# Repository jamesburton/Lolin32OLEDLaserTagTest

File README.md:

# Lolin32 OLED Laser Tag

Reverse-engineering, decoding, and transmitting **Vatos** infrared laser-tag
signals across two ESP32 boards:

- **Lolin32 OLED** (ESP32 + 128×32 SSD1306) — IR monitor / decoder / transmitter
  and the C# trainer feeder. Reads NEC remotes and Vatos shots to the OLED, and
  fires Vatos shots via an IR LED.
- **ESP32-S3-Matrix** (ESP32-S3 + 8×8 WS2812) — a wearable **target**: idles in
  a rainbow, tracks its own health, flashes the firing team's colour and goes
  briefly dark when hit, and holds dark when its health reaches zero.

Both boards support **wireless OTA updates and UDP telemetry** (see
[Wireless](#wireless)). A **network control plane** (REST + UDP) configures and
controls devices, with a **.NET client library** on the host side (see
[Control plane](#control-plane-v2)). Shared logic lives in libraries:
`lib/Vatos` (decode/encode), `lib/IrFramer` (IR edge framing), `lib/TagNet`
(WiFi + OTA + HTTP + UDP), and `lib/ControlProto` (the protocol-agnostic wire
codec for the control plane).

> The Vatos IR protocol is not documented publicly; the protocol description in
> `docs/gun-protocol.md` was reverse-engineered from scratch in this project.

---

## Table of contents

- [What it does](#what-it-does)
- [Hardware](#hardware)
- [Build, flash, monitor](#build-flash-monitor)
- [Wireless](#wireless)
- [Control plane (V2)](#control-plane-v2)
- [How it works](#how-it-works)
- [The Vatos protocol (reverse-engineered)](#the-vatos-protocol-reverse-engineered)
- [The Vatos library](#the-vatos-library)
- [The C# signal trainer](#the-c-signal-trainer)
- [The journey (how we got here)](#the-journey-how-we-got-here)
- [Repository layout](#repository-layout)
- [Future work](#future-work)

---

## What it does

- **Receives** 38 kHz IR and decodes it live:
  - **NEC** remotes → `address:command` (e.g. `0707:04`)
  - **Vatos** laser-tag shots → `team` + `damage` (e.g. `Blue 2`)
- **Displays** the decode on the on-board OLED, with a blink LED on every hit.
- **Transmits** valid Vatos shots via an IR LED (38 kHz carrier, correct frame
  + checksum), triggered by the BOOT button or any byte over serial.
- **Trains/recognises** signals from a PC via the C# `IrSignalTrainer` app,
  matching NEC codes exactly and other protocols by full-frame fingerprint.
- **Networks** the target: broadcasts discovery heartbeats and hit/state
  telemetry over UDP, serves a JSON REST API for config/control, accepts
  low-latency UDP control broadcasts, and is driven from a host-side **.NET
  client library** (see [Control plane](#control-plane-v2)).

---

## Hardware

### Carrier PCB (ESP32-S3-Matrix target)

A custom 100×80 mm 2-layer carrier board for the S3 target lives in
[`hardware/lasertag-carrier/`](hardware/lasertag-carrier/): socketed
ESP32-S3-Matrix, MAX98357A audio, microSD, IR RX + transistor IR-TX driver,
WS2812 strip output, OLED header, GP2 role selector, power switch and M3
mounting holes.

- **How to build/assemble it** (stage-by-stage, core vs optional blocks,
  jumper settings, bring-up):
  [`instructions/BUILD_LASERTAG_CARRIER_ESP32_MATRIX.md`](instructions/BUILD_LASERTAG_CARRIER_ESP32_MATRIX.md)
- **How it was made** (code → perf-board → Gerbers, tools/tips/gotchas):
  [`PCB_FROM_PLATFORMIO.md`](PCB_FROM_PLATFORMIO.md)
- **Fab package** (PCBWay-ready Gerber zip):
  [`hardware/lasertag-carrier/fab/lasertag-carrier-rev1-gerbers.zip`](hardware/lasertag-carrier/fab/lasertag-carrier-rev1-gerbers.zip),
  also attached to the
  [`pcb-carrier-rev1` release](../../releases/tag/pcb-carrier-rev1)
- **BOM**: [`hardware/lasertag-carrier/bom.csv`](hardware/lasertag-carrier/bom.csv);
  circuit spec: `.docs/pcb-blocks.md`
- **Ordering from PCBWay?** New users can use this referral link for **$5 off
  their first order**: <https://pcbway.com/g/2F9n3B>

### Lolin32 OLED (monitor / decoder / transmitter)

| Function | Pin | Notes |
| -------- | --- | ----- |
| OLED I²C | SDA = GPIO5, SCL = GPIO4 | SSD1306, **128×32**, address `0x3C` |
| IR receiver (VS1838B) | OUT = GPIO25 | demodulating; idles HIGH, pulses LOW |
| Activity LED | GPIO26 | blinks ~80 ms on each received frame |
| IR transmit LED | GPIO13 | 38 kHz carrier via the LEDC peripheral |
| Test-shot trigger | GPIO0 (BOOT) **or** serial | any serial line also fires a shot |

### ESP32-S3-Matrix (target)

| Function | Pin | Notes |
| -------- | --- | ----- |
| 8×8 WS2812 matrix | GPIO14 | on-board, 64 LEDs (NeoPixel) |
| IR receiver (VS1838B) | OUT = GPIO1 | GPIO10–14 are taken by the IMU/matrix |
| Activity LED | GPIO7 | blinks on each received frame |
| (reserved) | GPIO10–13 | on-board QMI8658 IMU |

Behaviour: rainbow when idle → on a Vatos hit, subtract the shot's damage from
its health (**max health 32**), flash the firing team's colour (Blue/Red/Green/White)
4×, then go dark for a brief configurable "stunned" interval (default ~1–5 s;
tune via the control plane) → resume rainbow, keeping accumulated damage. The
**4 central columns** of the 8×8 matrix form a **health bar**: they deplete
top-down as health drops (outer 4 columns stay rainbow). At **0 health** it
holds dark ("dead") until a respawn / reset. The device is **authoritative for
its own health** and emits `EVT hit` / `EVT state` telemetry as it changes (see
[Control plane](#control-plane-v2)). Matrix current is capped to 500 mA
(`setMaxPowerInVoltsAndMilliamps`) for USB safety.

Notes:

- The on-board OLED on this unit is a **128×32** SSD1306 (not the 128×64 the
  Lolin32 normally ships with). Driving it as 128×64 renders garbled,
  interlaced text — the `src/display_test.cpp` diagnostic cycles candidate
  driver/geometry configs to identify the right one.
- The OLED is **not** on the ESP32 default I²C pins, so `Wire.begin(5, 4)` is
  required.
- The receiver/transmit/indicator LEDs in this build are driven **without series
  resistors** at the ESP32's minimum drive strength (`GPIO_DRIVE_CAP_0`, ~5 mA)
  to protect the pins. This is fine for bench/loopback testing but limits IR
  transmit range — a transistor driver + resistor is needed for real range.

---

## Build, flash, monitor

[PlatformIO](https://platformio.org/) project (Arduino framework; boards
`lolin32` and `esp32-s3-devkitc-1`, plus a `native` env for unit tests).

```sh
pio run -e lolin32                                   # build
pio run -e lolin32 -t upload --upload-port COM14     # flash
pio device monitor -p COM14 -b 115200                # serial monitor
```

Environments:

- `lolin32` — Lolin32 firmware (`src/main.cpp`).
- `lolin32_displaytest` — the OLED config finder (`src/display_test.cpp`).
- `esp32-s3-matrix` — Matrix target firmware (`src/matrix_main.cpp`).
- `native` — host-compiled unit tests for `lib/ControlProto` (no board).
- `*-ota` — wireless-upload variants (see [Wireless](#wireless)).

```sh
pio run -e esp32-s3-matrix -t upload --upload-port COM7   # flash the Matrix
pio test -e native                                        # run ControlProto unit tests
```

### Flashing workaround (Lolin32)

This particular board has **no BOOT/EN buttons** and its USB auto-reset into the
bootloader is unreliable, so uploads may fail with
`Wrong boot mode detected (0x17)`. To flash:

1. Jumper **GPIO0 → GND**.
2. Run the upload — the chip now enters download mode and flashes.
3. **Remove the GPIO0–GND jumper** and reset (re-plug USB) so it boots normally.

If the board disappears from Windows entirely, unplug/replug the USB to
re-enumerate the CP210x serial port.

---

## Wireless

Both firmware targets bring up WiFi, ArduinoOTA, and UDP telemetry via the
shared `lib/TagNet` library.

### Set WiFi credentials (over serial)

Credentials are stored in NVS, set with serial commands (no rebuild):

```powershell
./tools/set-wifi.ps1 -Port COM14 -Ssid "MyNetwork" -Password "s3cret"
```

or manually in a serial monitor: `ssid <name>`, `pass <pw>`, `wifi-save`
(also `wifi-status`, `wifi-clear`). The board prints its IP once connected.

### Board-config overrides (cfg command)

A whitelisted subset of board-profile fields can be overridden at runtime
without a rebuild:

```
cfg <key> <value>
```

Examples: `cfg matrixOrder 1`, `cfg matrixPin 27`, `cfg activityLedPin 26`.
Changes are saved to NVS and applied on the next reboot.

### OTA updates

After one USB flash + WiFi provisioning, update over the air — no cable, no
GPIO0 jumper.

**For the S3 fleet, prefer the host's `ota` command** (see
[Game manager](#game-manager-host)): every board now runs 2.1.0, which serves
`POST /api/update`, so `ota all` flashes the whole fleet over HTTP with no
Python and no per-board IP chasing. The espota route below is now only needed
to **bootstrap a board running pre-2.1.0 firmware** (it has no `/api/update`),
and for the Lolin32.

```sh
pio run -e lolin32-ota -t upload          # -> lasertag-lolin32 (IP in platformio.ini)
pio run -e esp32-s3-matrix-ota -t upload  # -> lasertag-matrix  (IP in platformio.ini)
```

> ⚠ `ota all` sends **one binary to every online outdated board** and cannot
> tell an ESP32 from an ESP32-S3 (heartbeats carry no chip field). With the
> **Lolin32 (ESP32)** on the network alongside the S3 fleet, target it
> explicitly with `ota <id>` rather than `all`.

Both `*-ota` envs target the boards' **IP addresses** in `platformio.ini`.
mDNS (`lasertag-*.local`) resolves fine for ping/REST on this dev machine, but
espota is unreliable with mDNS names, so OTA sticks to IPs — resolve the
current one with `ping lasertag-matrix.local` (the matrix roams via DHCP) and
update `upload_port` if it changed, or set a DHCP reservation. OTA can take
several minutes over a weak link (low RSSI), but is reliable.

### Telemetry monitoring

Devices broadcast discovery heartbeats and hit/state telemetry as UDP lines on
port 4210 (see [Control plane](#control-plane-v2) for the grammar). The
`tools/TagMonitor` console app prints them raw:

```sh
dotnet run --project tools/TagMonitor
# lasertag-matrix HB id=752b38 ip=192.168.1.34 fw=2.1.0 team=2 mode=idle hp=32 online=1
# lasertag-matrix EVT hit victim=752b38 shooterTeam=2 dmg=2 proto=vatos hp=30 ts=12345
```

> `mode=` in a heartbeat is the board's **role** (`idle`/`target`/`scoreboard`),
> **not** the match phase — a board reads `mode=idle` throughout a running
> match. There is no per-board match-phase readback; the host is authoritative.

**Discovering boards:** listen to the heartbeat roster (TagMonitor, the host's
`devices`, or either manager) and give it **~30 s**. Don't port-scan the subnet
— it misses boards that answer slowly, and every board roams on DHCP, so any IP
written down here or in `platformio.ini` may already belong to something else.

> **No telemetry but REST works?** That's a missing inbound firewall rule **or**
> a lossy weak-RSSI link. Rule out the firewall with `tools/setup-firewall.ps1`
> (Windows, self-elevating) / `tools/setup-firewall.sh` (Linux/macOS).

---

## Control plane (V2)

A protocol- and mode-agnostic network layer for configuring, controlling, and
monitoring devices. **REST** (reliable, JSON) handles config/CRUD/status; **UDP**
(fast, fire-and-forget on port 4210) handles discovery, telemetry, and
low-latency broadcast control. Devices decode IR into a generic `TagEvent`
(behind an `IrProtocol` abstraction — Vatos is the first protocol) and teams are
a generic indexed set, so game modes and the host never hard-code Vatos.

The full design and the authoritative wire contract (with golden test vectors)
live in
[`docs/superpowers/specs/`](docs/superpowers/specs/2026-06-15-control-plane-contract.md).

### REST API (served by the device)

| Method | Route | Purpose |
| ------ | ----- | ------- |
| `GET` | `/api/status` | live runtime status (mode, hp, team, online, fw, uptime, rssi) |
| `GET` | `/api/config` | persisted config (deviceId, ownTeam, enabledTeams, protocolId, brightness, teamColours) |
| `PATCH` | `/api/config` | partial update; persists to NVS; unknown field → `400` |
| `POST` | `/api/mode` | set runtime `activeMode` + timings (not persisted) |
| `POST` | `/api/command` | one-shot actions: `identify`, `bright`, test `hit`, `debug` |

Identity + preferences persist in NVS; game state (mode, timings, health) is
runtime only, so a reboot returns the device to a neutral idle. **Write
requests must send `Content-Type: application/json`** — the ESP32 `WebServer`
discards a urlencoded body (curl's default); the .NET client sets the header
automatically. (`GET /` and `GET /cmd?c=` remain as deprecated aliases.)

### UDP line-protocol (port 4210)

One message per packet; device→broadcast lines are prefixed with the hostname.

```
HB  id=752b38 ip=192.168.1.24 fw=2.0.0 team=2 mode=idle hp=100 online=1   # heartbeat (~2 s)
EVT hit victim=752b38 shooterTeam=2 dmg=2 proto=vatos hp=80 ts=12345      # telemetry
EVT state s=stunned hp=80 ts=12500                                        # ready|idle|stunned|dead|respawn
CTL start ts=30000   |   CTL stop   |   CTL reset hp=100                  # host -> device control
```

`EVT`/`HB` come **from** the device; `CTL` is sent **to** devices. The device is
authoritative for its own health; the host tallies match state from the event
stream. Send `CTL` to the **subnet broadcast** (e.g. `192.168.1.255`) — the
limited broadcast `255.255.255.255` is not delivered on this LAN.

### .NET host library

`dotnet/LaserTag.Client` (net10.0) is the typed host client:

- `LaserTagClient` — REST client for `/api/*` (`GetStatusAsync`,
  `PatchConfigAsync`, `SetModeAsync`, `SendCommandAsync`, …).
- `UdpMessageParser` — parses `HB`/`EVT` lines into typed records; formats `CTL`.
- `DeviceRoster` — live roster with liveness timeout (6 s) + rejoin detection.
- `NetworkDiagnostics` — advisory firewall/port hints.

`dotnet/openapi/lasertag.yaml` describes the REST surface (for generating other
clients). `dotnet/LaserTag.Smoke` is a throwaway harness that exercises the
library against a live device; run it for a quick end-to-end check:

```sh
dotnet test  dotnet/LaserTag.sln                              # unit tests
dotnet run --project dotnet/LaserTag.Smoke -- 192.168.1.24 20 # live REST + UDP roster
```

### Game manager (host)

`dotnet/LaserTag.Host` orchestrates matches over the control plane (spec:
`docs/superpowers/specs/2026-07-12-game-manager-design.md`):

```sh
dotnet run --project dotnet/LaserTag.Host            # auto-detects the subnet broadcast
# devices | start dm 5m [--kill 5 --hit 1 --waves 30s] | start elim [--timer 10m]
# start chase <dur|--first N> [--min d] [--max d] [--gap d] [--penalty N] [--dark]
# score | stop | reset [id] | activate [id] | deactivate [id] | quit
# team <id|all> <0-4|none>  — assign a board's team (0/none = neutral target)
# teams split <n>           — deal the online roster round-robin into n sides
# fs ls|put|get|rm|play|startup <id> …  — manage sound clips in on-board flash
# fw [bin]                — fleet firmware table: running vs available (from the
#                           LTFW: marker embedded in firmware.bin)
# ota <id|all> [--force]  — push firmware over HTTP to online boards; `all`
#                           targets outdated boards only (--force re-pushes)
```

**Fleet OTA (firmware ≥ 2.1.0):** every board serves `POST /api/update`
(multipart firmware upload → verified flash → reboot) and a browser upload
form at `GET /update`, so updates work from the host CLI, a browser, or the
future phone app — no espota/python needed. Spec:
`docs/superpowers/specs/2026-07-27-fleet-ota-design.md`. Boards on older
firmware need one last espota flash to gain the endpoint.

### Sound clips in on-board flash (firmware ≥ 2.4.0)

Clips live in the board's **on-board flash**, in the partition table's
otherwise-unused 1.375 MB data partition (LittleFS). No microSD, no socket, no
wiring. Manage them remotely:

```sh
fs ls <id> [dir]              # storage usage + directory listing
fs put <id> <local> <remote>  # upload, e.g. fs put e45614 assets/sfx/startup-rise.wav /sfx/startup.wav
fs get <id> <remote> <local>  # download
fs rm  <id> <remote>          # delete (files only; directories are refused)
fs play <id> <remote>         # play a clip now
fs startup <id> <remote|none> # set/clear the power-on cue
```

REST equivalents on each board: `GET /api/files?path=`,
`POST|GET|DELETE /api/files/file?path=`, and
`POST /api/command {"cmd":"play","path":"…"}`.

**Clips must be 16 kHz / 16-bit / mono WAV** — the parser rejects anything else
rather than converting. Generate one with
`python tools/gen_sfx.py --wav out.wav --clip startup|death`, or convert any
source with
`ffmpeg -i in.mp3 -ac 1 -ar 16000 -sample_fmt s16 out.wav`.

**There is no clip length limit.** Playback streams from flash in chunks and
feeds the task watchdog, so clip size is bounded by the partition (~1.4 MB,
about four 10-second clips) rather than by free RAM. Both former limits are
gone: clips used to be capped at ~3 s by the watchdog, and at ~270 KB by having
to fit in the heap.

> **Startup sound defaults to none.** Set it per board with `fs startup`; it is
> stored as `startupSfx` and played once at the end of boot. An unset, missing
> or malformed clip is skipped silently so a board always comes up.

> Clips **survive firmware updates** — OTA replaces the app partition only.

> A clip that no config field references is reachable *only* via the API, which
> is how to keep a "secret" sound with no on-board trigger.

> Every caller-supplied path is validated on the device: absolute, no `..`
> segment. That check is the only thing between a LAN request and the
> filesystem, so it is unit-tested natively.

**microSD is optional and currently unproven.** The code remains (`sdprobe`,
`sdpins`, `sdscan` are useful hardware diagnostics), but no board here has ever
mounted a card — see the handoff for the electrical findings.

### Teams (firmware ≥ 2.2.0)### Teams (firmware ≥ 2.2.0)

A device's team lives in its **persisted config** (`ownTeam`), not the control
plane: a match reads each board's team from its heartbeat and snapshots it when
the lobby forms. Assign teams from any surface:

```sh
# Host CLI
team <id|all> <0-4|none>   # one board, or the whole roster
teams split <n>            # deal the online roster round-robin into n sides

# Web / Android manager: the team buttons on each Devices card
# JSON API
curl -X POST http://<host>:5080/api/team -H 'content-type: application/json' \
     -d '{"id":"752b38","team":1}'
```

**Team 0 = `none` = a neutral target, and it is the default.** A neutral board
is shootable by everyone, hits on it score for the *shooter's* team, and it can
never win a match — the right default for a target that isn't playing for a
side. This matches what the firmware has always done physically: it has never
own-team filtered, so every decoded shot damages the board that receives it.
Boards provisioned before 2.2.0 keep whatever team they were given (most were
2); `team all none` resets them.

> `teams split` uses a stable order (by device id), so the same fleet always
> splits the same way rather than reshuffling sides between matches.

> ⚠ **Teams take effect from the next match.** The lobby fixes each
> participant's team at start, so reassigning mid-round does not move a player —
> that would silently rewrite who the existing scores belonged to.

> ⚠ **The lobby is fixed at match start.** Devices that come online after the
> countdown are ignored for the rest of the match (a device that *drops and
> returns* does rejoin, and gets a re-issued `CTL start id=`).

Match rules live in `dotnet/LaserTag.Game` (`IGameMode`: Deathmatch,
Elimination, Chase — see `docs/superpowers/specs/2026-07-27-chase-mode-design.md`).
Scoring is per-team — the IR protocol carries the shooter's team, not a
player id. CTL grammar v2 (`countdown`, `gameover`, `activate`/`deactivate`,
optional `id=` addressing) is emitted by the host today.

Boards double as scoreboards during any match — the host pushes CTL Score
updates on change plus a 1 s live refresh, so a board's own OLED/matrix shows
the running score without extra wiring. A board can also run standalone as a
dedicated scoreboard outside of a match via `POST /api/mode {"mode":
"scoreboard"}`.

**Firmware compatibility:** firmware at or above this build enforces `id=`
addressing, so an `id=`-addressed `reset`/`start`/`activate`/`deactivate`
only reaches the targeted device. Boards still running older firmware ignore
the `id=` filter and apply addressed CTLs to every device on the arena —
reflash all boards to the current firmware before running a multi-device
match.

---

## Managers: web and Android

Two graphical front ends for running a game, alongside the console REPL. Both
render **the same screens from the same code** and run **the same match engine** —
they differ only in which machine the engine runs on.

```
        LaserTag.Ui (Blazor screens + IGameSession)
                    /                \
      LaserTag.Web                    LaserTag.App
   engine on the PC                engine on the phone
                    \                /
              LaserTag.Runtime (GameService, UDP listener, 4 Hz tick)
                    LaserTag.Game + LaserTag.Client
```

Screens: **Devices** (roster with identify/reset/activate per board), **Match**
(mode picker with per-mode parameters, start/stop), **Live** (scoreboard, player
table, event feed), **Firmware** (running-vs-available versions and one-tap OTA,
reusing the fleet-OTA pipeline).

### Web manager

```sh
dotnet run --project dotnet/LaserTag.Web            # http://<pc-ip>:5080
dotnet run --project dotnet/LaserTag.Web -- --broadcast 192.168.1.255
```

Binds `0.0.0.0:5080` over plain HTTP so any phone or laptop on the LAN can open
it — no install, and iPhone guests work too. A PC must be running at play time.

A JSON API sits alongside the UI for scripting:

| Endpoint | Purpose |
| -------- | ------- |
| `GET /api/devices` | Roster with team, hp, firmware, online |
| `GET /api/match` | Phase, clock, scores, players |
| `POST /api/match/start` | Body e.g. `{"mode":"chase","duration":"2m","firstTo":5}` |
| `POST /api/match/stop` | Stop the running match |
| `POST /api/control` | e.g. `{"kind":"activate","id":"eb20f8","t":1500}` |

### Android manager (the phone is the host)

```sh
dotnet build dotnet/LaserTag.App -f net10.0-android
dotnet publish dotnet/LaserTag.App -f net10.0-android -c Release -p:AndroidPackageFormat=apk
# -> dotnet/LaserTag.App/bin/Release/net10.0-android/publish/com.jamesburton.lasertag-Signed.apk
```

The phone binds UDP 4210, runs the engine and broadcasts CTL itself, so **no PC
is needed at play time** — the point of the exercise. Requires the
`maui-android` workload (`dotnet workload install maui-android`).

Two Android-specific traps are handled in code, both of which produce a
silently-empty roster rather than an error:

- **Multicast lock.** Android drops inbound broadcast UDP unless the app holds a
  `WifiManager.MulticastLock`. `AndroidMulticastGuard` holds one for the
  listener's lifetime; the manifest needs `CHANGE_WIFI_MULTICAST_STATE`.
- **MAUI never starts hosted services.** Unlike the Generic Host, `MauiApp`
  builds a service provider but does not run `IHostedService`, so the listener
  and tick loop are started explicitly in `App.OnStart`.

| Android app | Web manager |
| ----------- | ----------- |
|  |  |

> **Status:** the Android app **runs** — installed and driven on an Android 15
> emulator, where the shared screens render, navigation works and broadcast
> discovery picked up the right subnet. What is **still unverified** is the one
> thing that matters most: **receiving real telemetry**. An emulator sits behind
> NAT, so host broadcasts never reach it, and the multicast lock therefore could
> not be exercised. Treat the first run on a real phone, on the same Wi-Fi as
> the boards, as the true test.

## Board capability HAL

Each board is described by a compile-time `BoardProfile` struct (selected with
`-D BOARD_LOLIN32` or `-D BOARD_S3_MATRIX` in `platformio.ini`) that declares
its capabilities: IR rx/tx pins, hit-display type (WS2812 matrix, 3-pin RGB, or
none), OLED geometry, audio output (piezo or I2S DAC stub), and NVS storage.
Firmware and game-mode code target the HAL — `HitDisplay`, `IrTx`, `Sound` —
rather than raw pins, so the same game logic runs on any profiled board.

A whitelisted subset of profile fields (e.g. matrix data pin, pixel order,
activity LED pin) can be overridden at runtime via the `cfg <key> <value>`
serial command (see [Board-config overrides](#board-config-overrides-cfg-command));
overrides are persisted in NVS and applied at boot.

---

## How it works

### Receive path

An interrupt on the receiver pin timestamps every edge. Edges are grouped into
**frames** separated by ≥ 50 ms of silence (chosen so the gun's full-auto bursts
stay within one frame). Each completed frame is:

1. attempted as **NEC** (leader + 32 bits, validated by the command/inverse
   byte) → emits `NEC addr=0x.... cmd=0x..`;
2. otherwise, if it is 41 edges, attempted as **Vatos** → emits
   `VATOS team=N(name) dmg=N`;
3. always emitted raw as `FRAME n=.. data=L..,H..,...` for fingerprinting.

The optional decoded line is printed **before** the `FRAME` line so a consumer
can attach it to the frame that terminates the event.

> **Verified board-to-board (2026-07-29):** an IR-TX-equipped board firing at
> another decodes exactly — all four damage values cost exactly their damage,
> and all four shooter teams arrive correctly in `EVT hit shooterTeam=`.
> Two things to know when testing: range is very short on a raw GPIO drive
> (aim the boards at each other, close), and **shots arriving during the
> post-hit flash/stun window are ignored by design** (`applyHit` runs only in
> the rainbow idle state), so space test shots ~4 s apart — a rapid burst
> looks like a fault but isn't.

### Transmit path

`Vatos::encode()` builds the 41-symbol bit pattern for a `{team, damage}` shot
(including the correct checksum). The firmware then gates a 38 kHz LEDC carrier:
even symbols are IR bursts (carrier on), odd symbols are gaps, each lasting
~380 µs (`0`) or ~800 µs (`1`). Pointing the IR LED at the VS1838B closes a full
**loopback**: transmitted shots are received and decoded by the same board.

### Serial protocol (115 200 baud)

```
NEC addr=0x0707 cmd=0x04            # optional, precedes its FRAME
VATOS team=1(Blue) dmg=2           # optional, precedes its FRAME
FRAME n=75 data=L4520,H4490,...    # always; H/L = level held, value = µs
TX team=1(Blue) dmg=2              # printed when a shot is transmitted
```

---

## The Vatos protocol (reverse-engineered)

A Vatos shot is a **41-edge frame** on a ~38 kHz carrier: 21 IR bursts
interleaved with 20 gaps (it starts and ends with a burst). Every symbol is
short (~380 µs = `0`) or long (~800 µs = `1`); quantising at 600 µs gives a
stable 41-bit pattern.

The frame encodes the firing **team** and the shot's **damage** — *not* the
weapon:

| Field | Bits (MSB-first) | Values |
| ----- | ---------------- | ------ |
| Preamble / framing | 0–21 | constant |
| **Team** | 22–24 | Blue=`001`(1), Red=`010`(2), Green=`011`(3), White=`100`(4) |
| Separator | 25–29 | constant |
| **Damage** | 30–32 | `001`–`100` = damage 1–4 |
| Separator | 33–36 | constant `0000` |
| Checksum | 37–40 | fixed (nonlinear) function of team + damage |

### Key findings

- **It encodes damage, not weapon.** Per the manual: Pistol = 1, Shotgun = 2,
  SMG = 2, MG = 3, Rocket = 4. Because **Shotgun and SMG both deal damage 2,
  they transmit an identical frame** — no receiver can tell them apart. So each
  gun emits at most 4 distinct codes per team (4 teams × 4 damage = 16 total).
- **The audio is mislabelled on this unit:** the spoken "Machine Gun" / "Sub
  Machine Gun" names are swapped relative to the damage actually sent. Identify
  shots by damage, not the voice line.
- **Carrier is ~38 kHz**, confirmed because the (38 kHz) VS1838B demodulates the
  gun cleanly. No 56 kHz receiver needed.
- **Both bursts and gaps carry payload.** An early fingerprint that used only the
  gap durations collided distinct shots (for some teams, damage 2 and damage 3
  share gap patterns and differ only in the bursts). The working approach
  fingerprints/decodes the full frame.

The full derivation, the 16-code matrix, and the bit map are in
[`docs/gun-protocol.md`](docs/gun-protocol.md).

---

## The Vatos library

`lib/Vatos/` is a platform-independent decoder/encoder (no Arduino
dependencies — carrier generation lives in the caller):

```cpp
namespace Vatos {
  struct Shot { uint8_t team; uint8_t damage; };          // team 1-4, damage 1-4

  bool decode(const uint32_t *edgeDurationsUs, size_t count, Shot &out);
  bool encode(const Shot &shot, bool bits[FrameEdges]);    // FrameEdges == 41
  const char *teamName(uint8_t team);                      // "Blue".."White"
}
```

- `decode()` quantises 41 edge durations, validates the constant framing **and**
  the checksum, and extracts team + damage.
- `encode()` produces the 41-symbol pattern (even indices = bursts) for
  transmission, with the correct checksum from a 4×4 lookup table.

Both directions were verified by full **TX → IR → RX → decode** loopback across
multiple team/damage codes, and `decode()` was verified against real gun fire.

---

## RF (2.4 GHz) probe — CLOSED, no signal found

A side investigation into whether the Vatos kit also uses a 2.4 GHz link
alongside its IR. **Result: nothing was detected**, and the leading explanation
is that these gun-only units have no radio — see
[docs/rf-protocol.md](docs/rf-protocol.md) for the evidence and the retractions.

The tooling works and is kept for if the question reopens. An nRF24L01+ wired to
an ESP8266 (`pio run -e esp8266-rfprobe`) provides five serial commands:

| Command | Purpose |
| ------- | ------- |
| `selftest` | Reads back written registers — proves the SPI wiring |
| `scan [sweeps]` | Fast sweep of all 126 channels via the power detector |
| `watch from= to= ms=` | Dwells per channel; far more sensitive to short bursts |
| `dwell ch= secs=` | Camps on one channel, 100 ms buckets for event correlation |
| `sniff ch= rate= secs=` | Promiscuous capture (2-byte address, CRC off) |

Wiring: CE=GPIO4, CSN=GPIO5, SCK=GPIO14, MOSI=GPIO13, MISO=GPIO12, 3V3 with a
10 µF cap at the module. Captured `RF …` lines are analysed by the
**`LaserTag.Rf`** library (CRC16 validation, bit realignment, address recovery);
only a CRC-valid packet counts as a detection. Occupancy figures never do — that
lesson cost an evening and is written up in the findings doc.

## The C# signal trainer

`tools/IrSignalTrainer/` is a .NET console app that reads the board's serial
output and tags signals against named devices and buttons (see
[`tools/README.md`](tools/README.md)).

```sh
dotnet run --project tools/IrSignalTrainer            # COM14, signatures.json
```

- **NEC** signals match **exactly** on the decoded `address:command` code.
- **Other** signals (e.g. the gun, before firmware decoding existed) match on a
  quantised **full-frame** bit signature.
- `t` trains (device + button, 4 samples), `l` lists, `q` quits. The library is
  persisted to `signatures.json`.

`signatures.json` in the repo contains an example library trained on a TV remote
(NEC) and the Vatos gun.

---

## The journey (how we got here)

A condensed log of the build, because most of the value was in the process:

1. **Board bring-up.** Adapted the manufacturer OLED example to PlatformIO and
   verified the display + serial. Discovered the panel is 128×**32**, not
   128×64 — the cause of unreadable, interlaced text — using a config-finder
   sketch.
2. **Sensor selection.** Started with a KEYES photodiode + LM393 comparator
   board. It is not a demodulating receiver, so its output fragmented/merged and
   needed constant potentiometer tuning. Swapped to a **VS1838B**, which
   produced clean, decode-grade frames with no tuning. (See
   `docs/sensor-comparison.md`.)
3. **NEC decoding.** Added an NEC decoder to the firmware (OLED shows
   `addr:cmd`) and validated it against a TV remote (address `0x0707`).
4. **Cracking the gun.** The gun was not NEC. Captured frames, decoded the
   structure, and — crucially, with the owner's manual + the spotted audio/icon
   mismatch — realised the IR encodes **team + damage**, which explained an
   apparent "Shotgun = Machine Gun" collision (it is really Shotgun = SMG, both
   damage 2). Captured the full 4-team × 4-damage matrix and isolated the team,
   damage, and checksum bit-fields.
5. **Library + transmit.** Factored the decode/encode into `lib/Vatos/`, added a
   38 kHz IR transmitter, and verified the whole chain by loopback.

---

## Repository layout

```
platformio.ini            PlatformIO config (lolin32 / displaytest / matrix + OTA + native)
src/
  main.cpp                Lolin32: RX + NEC/Vatos decode, OLED, IR transmit
  matrix_main.cpp         ESP32-S3-Matrix: 8x8 LED target + V2 control plane
  display_test.cpp        OLED driver/geometry config finder (separate env)
lib/
  Vatos/                  Platform-independent Vatos decode/encode
  IrFramer/               Shared IR edge-framing (ISR + frame assembly)
  TagNet/                 Shared WiFi (serial creds) + OTA + UDP + HTTP server
  ControlProto/           Protocol-agnostic control-plane wire codec + TagEvent
  Board/                  Compile-time BoardProfile per board (pins, capabilities)
  HitDisplay/             WS2812 matrix / RGB hit-feedback output HAL
  IrTx/                   IR transmit HAL
  Sound/                  Sound cues (piezo; I2S DAC stub)
  BoardNvs/               NVS override load + cfg serial command
test/
  test_board/             Native unit tests for Board/BoardNvs
  test_controlproto/      Native (host-compiled) unit tests for ControlProto
dotnet/                   .NET 10 host ecosystem (LaserTag.sln)
  LaserTag.Client/        Typed REST + UDP client library (parser, roster, client)
  LaserTag.Client.Tests/  xUnit tests
  LaserTag.Smoke/         Throwaway live smoke harness
  openapi/lasertag.yaml   OpenAPI description of the REST surface
tools/
  IrSignalTrainer/        C# serial trainer + signature library
  TagMonitor/             C# UDP telemetry listener
  set-wifi.ps1            Provision WiFi credentials over serial
  setup-firewall.ps1/.sh  Check/fix the host firewall for UDP 4210 telemetry
docs/
  device-info.md          Lolin32 board pinout and OLED details
  sensor-comparison.md    KEYES comparator board vs VS1838B
  gun-protocol.md         The reverse-engineered Vatos IR protocol
  superpowers/specs/      Control-plane design + authoritative wire contract
signatures.json           Example trained signature library (TV remote + gun)
```

---

The V2 **control plane** (REST + UDP config/control/telemetry, device-side
health, the .NET client library) is in place. Next:

- **Firmware game-mode framework + "Team Colours" mode** — pluggable modes on
  top of the `activeMode`/timings plumbing already wired through the control
  plane.
- **Host scoring & orchestration** — tally match state from the `EVT` stream;
  multi-device game start/stop via `CTL` broadcasts.
- **.NET CLI + Claude skill** — a runnable CLI over `LaserTag.Client` (the
  library exists; its `CTL` sender must target the subnet broadcast), wrapped as
  a Claude skill.
- **Real transmit range** — a transistor driver + series resistor on the IR LED
  for gameplay distances rather than bench loopback.
- **Pin down the checksum formula** — currently a verified 4×4 lookup; the exact
  algorithm (symmetric in team+damage) is not yet derived.

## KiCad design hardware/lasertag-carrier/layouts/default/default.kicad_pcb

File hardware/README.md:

# hardware/ — KiCad PCB project

Custom carrier/breakout PCB for the laser-tag platform. Starts with the
**ESP32-S3-Matrix carrier** (full scope: audio, microSD, IR RX/TX, I2C OLED,
external WS2812 out, power in; optional separate level-shifter board).

## Source of truth
- **`../.docs/pcb-blocks.md`** — netlist-level block spec (pin-to-pin tables, BOM).
  KiCad generation is mechanical from these tables.
- **`../.docs/pcb-design.md`** — higher-level decisions + toolchain rationale.
- **`../.docs/handoff.md`** §Board BOM — the discrete circuitry summary.

The circuit was agreed 2026-07-04 (see the "RECONCILED" note in `pcb-blocks.md`):
IR TX on **GP37** (2N2222A + 33Ω from 5V driver), 0.1″ connectors throughout,
power LED, optional microSD LDO, audio SD hard-mute on a GP2 solder-jumper.

## Toolchain (see `pcb-design.md` for the full rationale)
- **Schematic = file-based** via `kicad-skip` (edits `.kicad_sch` S-expr) or SKiDL
  (code → netlist). **KiCad v10 has no schematic API**, so the MCP can't do this.
- **Exports** (Gerbers / BOM / DRC / netlist) via `kicad-cli` (KiCad 10.0.3 at
  `C:\Program Files\KiCad\10.0\bin\kicad-cli.exe`).
- **`kicad-mcp` is PCB-layout only** — registered in `../.mcp.json` for the later
  routing phase; needs a session reload to activate. Not used for schematic.
- **Wokwi `diagram.json`** (in `../sim/wokwi/`) is generated one-way from the KiCad
  netlist for firmware/wiring simulation.

`KICAD_SEARCH_PATHS` (in `../.mcp.json`) points here.

## Status
Scaffold. Schematic capture pending (next step: `kicad-skip`/SKiDL from the
`pcb-blocks.md` tables). Layout/routing/fab gated on the pin freeze (handoff #1/#5,
now largely landed).

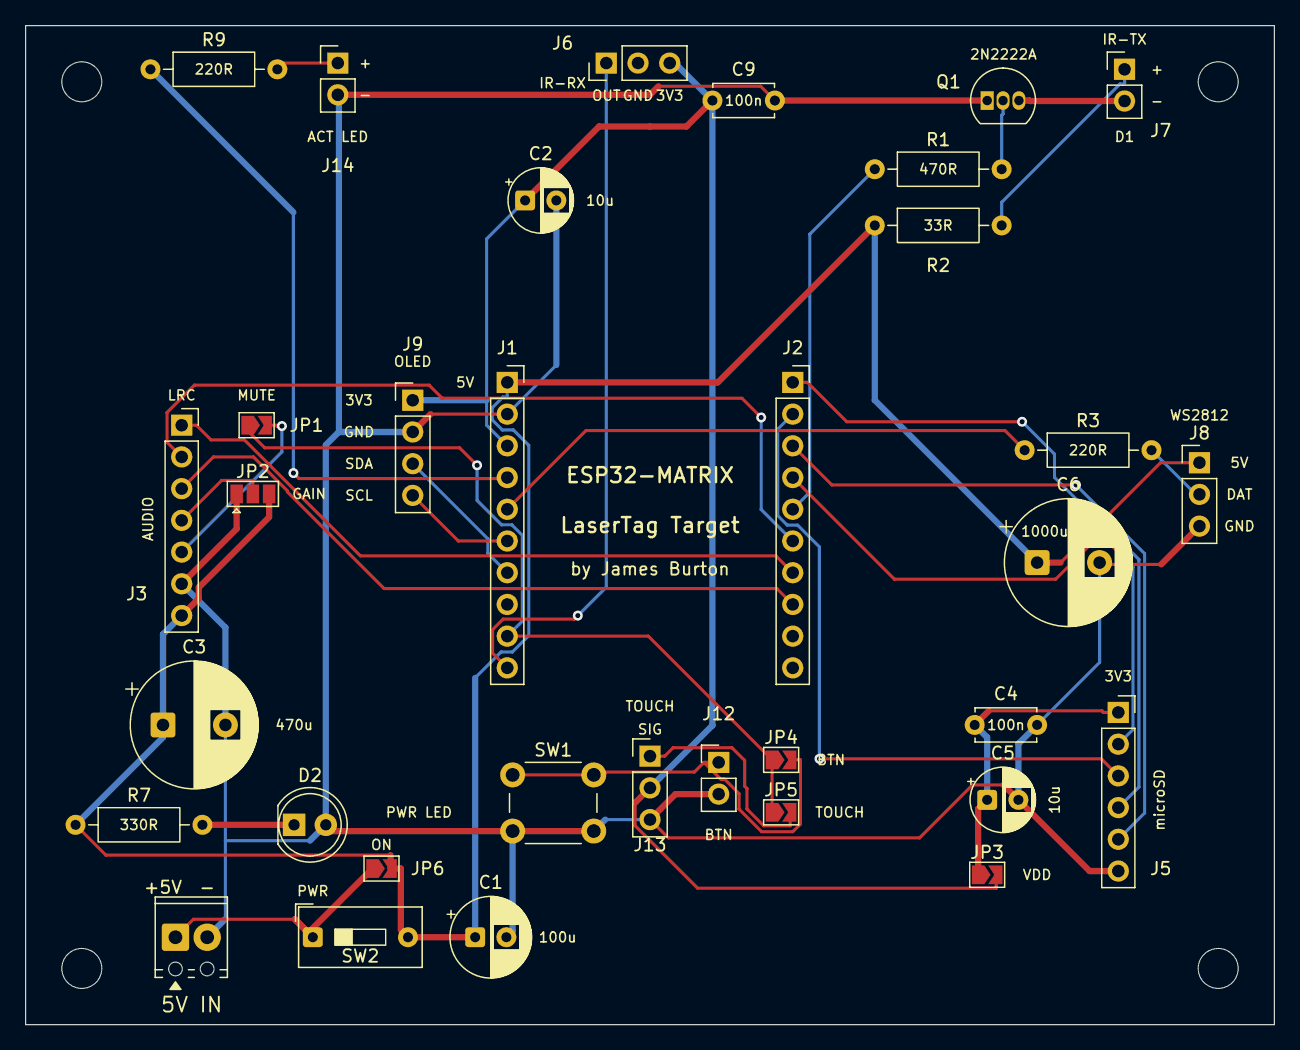
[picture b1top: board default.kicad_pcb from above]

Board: 2 copper layers, 100.0 x 80.0 mm, 38 parts (0 on the bottom side), 29 nets.

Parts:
C1: 100uF/10V; CP_Radial_D6.3mm_P2.50mm
C2, C5: 10uF/10V; CP_Radial_D5.0mm_P2.50mm
C3: 470uF/10V; CP_Radial_D10.0mm_P5.00mm
C4, C9: 100nF; C_Disc_D4.7mm_W2.5mm_P5.00mm
C6: 1000uF/10V; CP_Radial_D10.0mm_P5.00mm
D2: Power LED; LED_D5.0mm
H1, H2, H3, H4: M3; MountingHole_3.2mm_M3
J0: Power in 2P; TerminalBlock_Phoenix_MPT-0,5-2-2.54_1x02_P2.54mm_Horizontal
J1: S3-Matrix L; PinSocket_1x10_P2.54mm_Vertical
J2: S3-Matrix R; PinSocket_1x10_P2.54mm_Vertical
J3: MAX98357A; PinSocket_1x07_P2.54mm_Vertical
J5: microSD; PinSocket_1x06_P2.54mm_Vertical
J6: IR RX; PinHeader_1x03_P2.54mm_Vertical
J7: IR LED; PinHeader_1x02_P2.54mm_Vertical
J8: WS2812 out; PinHeader_1x03_P2.54mm_Vertical
J9: OLED I2C; PinHeader_1x04_P2.54mm_Vertical
J12: Ext button; PinHeader_1x02_P2.54mm_Vertical
J13: Touch hdr; PinHeader_1x03_P2.54mm_Vertical
J14: Activity LED; PinHeader_1x02_P2.54mm_Vertical
JP1: SD mute; SolderJumper-2
JP2: GAIN strap; SolderJumper-3
JP3: SD_VDD sel; SolderJumper-2
JP4: GP2-button; SolderJumper-2
JP5: GP2-touch; SolderJumper-2
JP6: always-on; SolderJumper-2
Q1: 2N2222A; TO-92_Inline
R1: 470R; R_Axial_DIN0207_L6.3mm_D2.5mm_P10.16mm_Horizontal
R2: 33R; R_Axial_DIN0207_L6.3mm_D2.5mm_P10.16mm_Horizontal
R3, R9: 220R; R_Axial_DIN0207_L6.3mm_D2.5mm_P10.16mm_Horizontal
R7: 330R; R_Axial_DIN0207_L6.3mm_D2.5mm_P10.16mm_Horizontal
SW1: SW_PUSH_6mm; SW_PUSH_6mm_H5mm
SW2: PWR switch; SW_DIP_SPSTx01_Slide_9.78x4.72mm_W7.62mm_P2.54mm

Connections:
ACT_LED: J1.4, R9.1
GND: C1.2, C2.2, C3.2, C4.2, C5.2, C6.2, C9.2, D2.2, J0.2, J1.2, J3.6, J5.6, J6.2, J8.3, J9.2, J12.2, J13.3, J14.2, JP2.1, Q1.1, SW1.2
VCC3V3: C2.1, C9.1, J1.3, J6.3, J9.1, J13.2, JP3.2
VCC5: C1.1, C3.1, C6.1, J1.1, J3.7, J8.1, JP2.3, JP6.2, R2.1, R7.1, SW2.2
VCC5_IN: J0.1, JP6.1, SW2.1
act_led_a: J14.1, R9.2
anode: D2.1, R7.2
audio-a: J1.9, JP1.1, JP4.1, JP5.1
audio-b: J3.5, JP1.2
base: Q1.2, R1.2
collector: J7.2, Q1.3
common: J3.4, JP2.2
footprint-_1: J7.1, R2.2
footprint-_2: J8.2, R3.2
footprint-a: J12.1, JP4.2, SW1.1
footprint-b: J13.1, JP5.2
i2c_scl: J1.6, J9.4
i2c_sda: J1.7, J9.3
i2s_bclk: J2.6, J3.2
i2s_din: J2.8, J3.3
i2s_ws: J2.7, J3.1
ir_rx: J1.10, J6.1
ir_tx: J2.5, R1.1
sd_cs: J2.4, J5.2
sd_miso: J2.3, J5.5
sd_mosi: J2.2, J5.3
sd_sck: J2.1, J5.4
sd_vdd: C4.1, C5.1, J5.1, JP3.1
ws_data: J1.5, R3.1

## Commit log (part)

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2026-06-12 Added .gitignore
2026-06-16 Test BoardProfile override validation + safe fallback
    Adds 4 Unity tests covering applyOverride: valid pin write, unknown key
    ignored, out-of-range pin rejected (unchanged), and matrixOrder enum round-trip.
